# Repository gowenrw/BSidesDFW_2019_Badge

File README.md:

# BSidesDFW_2019_Akira_Badge

This is where all the files for the BSidesDFW 2019 Akira Badge will be stored.  
This includes code and art and cad and fab files.  All the things.

## File Structure

This is the file structure of this repository

* [/](/README.md) - YOU ARE HERE
* [/eda/](./eda/) - Electronic Design Automation files for the badge PCB (EDA is KiCad)
  * ./BSidesDFW_2019/ - KiCad 5.x project folder for the BSidesDFW 2019 badge
  * ./HHV_2019_SC/ - KiCad 5.x project folder for the HHV Soldering Challenge board
  * ./CH552G_dev_board/ - KiCad 5.x project folder for the CH552G development board
* [/code/](./code/) - Code for programming the badge
  * ./BSidesDFW_badge/ - Code for the BSidesDFW_2019_Badge
  * ./CH552G_dev_board/ - Code for the CH552G dev board
  * ./CH552T_dev_board/ - Code for the CH552T dev board designed by WrickertH552    
  * ./ugly_dev_board/ - Code for the Ugly Dev Board CH552 Proof of Concept
  * ./include/ - Includes for the 55X chipset used in all the above
* [/docs/](./docs/) - Documentation created by this project related to the badge
* [/graphics/](./graphics/) - Artwork and other graphics created by this project for the badge
* [/reference/](./reference/) - Documentation pulled from other sources related to the badge components
  * ./battery-holder/ - Reference Materials related to battery holders.
  * ./button/ - Reference Materials related to buttons.
  * ./capacitor/ - Reference Materials related to capacitors.
  * ./ch55x/ - Reference Materials related to the CH55x micro-controller.
  * ./LED/ - Reference Materials related to LEDs.
  * ./resistor/ - Reference Materials related to resistors.
  * ./switch/ - Reference Materials related to the switches.
  * ./USB-connector/ - Reference Materials related to USB connectors.
* ./README.md - This File
* ./LICENSE - Currently set to MIT but open to changing it

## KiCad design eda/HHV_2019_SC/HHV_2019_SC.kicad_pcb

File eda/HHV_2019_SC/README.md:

# BSidesDFW_2019_Badge / Electronic Design Automation / Hardware Hacking Village 2019 Soldering Challenge

This is where all the KiCad 5.x files related to the BSidesDFW Hardware Hacking Village 2019 Soldering Challenge board

## File Structure

This is the file structure of this repository

* [/](/README.md) - Home
* [/eda](/eda/) - Electronic Design Automation files for the badge PCB (EDA is KiCad)
  * [/eda/HHV_2019_SC/](/eda/HHV_2019_SC/) - YOU ARE HERE
    * ./<filename>.pro - project file. Holds parameters that apply to the entire project (schematic and PCB layout).
    * ./<filename>.sch - schematic file.
    * ./<filename>.kicad_pcb - the new PCB layout file.
    * ./<filename>.net - netlist in "Pcbnew" format
    * ./<filename>.bak - backup of schematic file.
    * ./<filename>.kicad_pcb-bak - backup of the new PCB layout file.
    * ./<filename>-cache.lib - a local cache copy of all the symbols used in the schematic
    * ./fp-lib-table - Footprint library list
    * ./sym-lib-table - Schematic library list
    * [./3d_models/](/eda/HHV_2019_SC/3d_models/) - This directory contains footprint 3d model files
    * [./gerber/](/eda/HHV_2019_SC/gerber/) - This directory contains gerber formatted files for manufacturing
    * [./lib_fp/](/eda/HHV_2019_SC/lib_fp/) - This directory contains footprint module directories
    * [./lib_sh/](/eda/HHV_2019_SC/lib_sh/) - This directory contains schematic library files
    * [./pdf/](/eda/HHV_2019_SC/pdf/) - This directory contains pdf prints of schematics and cad files

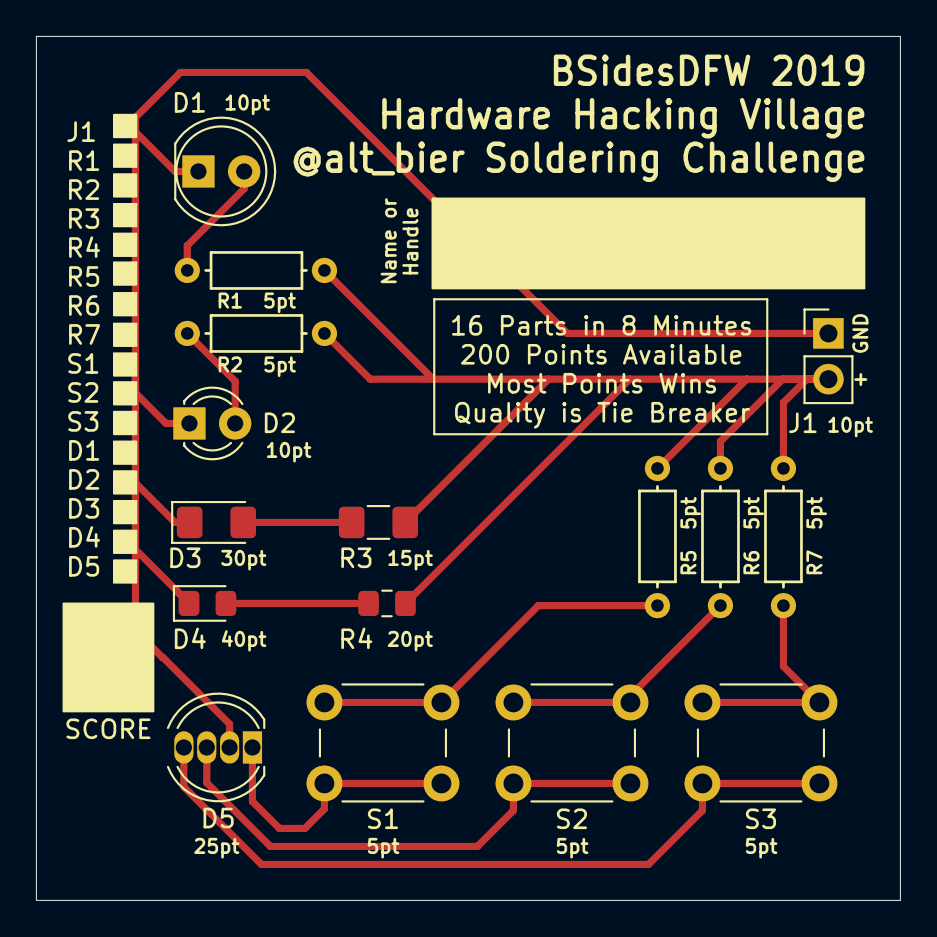
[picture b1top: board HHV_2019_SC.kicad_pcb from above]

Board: 2 copper layers, 48.0 x 48.0 mm, 16 parts (0 on the bottom side), 12 nets.

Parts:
D1: LED_5mm; LED_D5.0mm
D2: LED_3mm; LED_D3.0mm
D3: LED_1206; LED_1206_3216Metric_Pad1.42x1.75mm_HandSolder
D4: LED_0805; LED_0805_2012Metric_Pad1.15x1.40mm_HandSolder
D5: LED_RCBG_THT_5mm; LED_D5.0mm-4_RGB
J1: Battery_Connector; Pin_Header_Straight_1x02_Pitch2.54mm
R1, R2, R5, R6, R7: R_THT; R_Axial_DIN0207_L6.3mm_D2.5mm_P7.62mm_Horizontal
R3: R_1206; R_1206_3216Metric_Pad1.42x1.75mm_HandSolder
R4: R_0805; R_0805_2012Metric_Pad1.15x1.40mm_HandSolder
S1, S2, S3: SW_Push_Dual_THT_6mm; SW_PUSH_6mm

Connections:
GND: D1.1, D2.1, D3.1, D4.1, D5.2, J1.1
unnamed: D1.2, R1.2
unnamed: D2.2, R2.2
unnamed: D3.2, R3.2
unnamed: D4.2, R4.2
unnamed: D5.1, S1.1
unnamed: D5.3, S2.1
unnamed: D5.4, S3.1
unnamed: R5.2, S1.2
unnamed: R6.2, S2.2
unnamed: R7.2, S3.2
POS: J1.2, R1.1, R2.1, R3.1, R4.1, R5.1, R6.1, R7.1

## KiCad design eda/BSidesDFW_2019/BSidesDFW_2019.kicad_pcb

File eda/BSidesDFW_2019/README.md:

# BSidesDFW_2019_Badge / Electronic Design Automation / Main Badge

This is where all the KiCad 5.x files related to the main badge

## File Structure

This is the file structure of this repository

* [/](/README.md) - Home
* [/eda](/eda/) - Electronic Design Automation files for the badge PCB (EDA is KiCad)
  * [/eda/BSidesDFW_2019/](/eda/BSidesDFW_2019/) - YOU ARE HERE
    * ./<filename>.pro - project file. Holds parameters that apply to the entire project (schematic and PCB layout).
    * ./<filename>.sch - schematic file.
    * ./<filename>.kicad_pcb - the new PCB layout file.
    * ./<filename>.net - netlist in "Pcbnew" format
    * ./<filename>.bak - backup of schematic file.
    * ./<filename>.kicad_pcb-bak - backup of the new PCB layout file.
    * ./<filename>-cache.lib - a local cache copy of all the symbols used in the schematic
    * ./fp-lib-table - Footprint library list
    * ./sym-lib-table - Schematic library list
    * [./3d_models/](/eda/BSidesDFW_2019/3d_models/) - This directory contains footprint 3d model files
    * [./gerber/](/eda/BSidesDFW_2019/gerber/) - This directory contains gerber formatted files for manufacturing
    * [./lib_fp/](/eda/BSidesDFW_2019/lib_fp/) - This directory contains footprint module directories
    * [./lib_sh/](/eda/BSidesDFW_2019/lib_sh/) - This directory contains schematic library files
    * [./pdf/](/eda/BSidesDFW_2019/pdf/) - This directory contains pdf prints of schematics and cad files

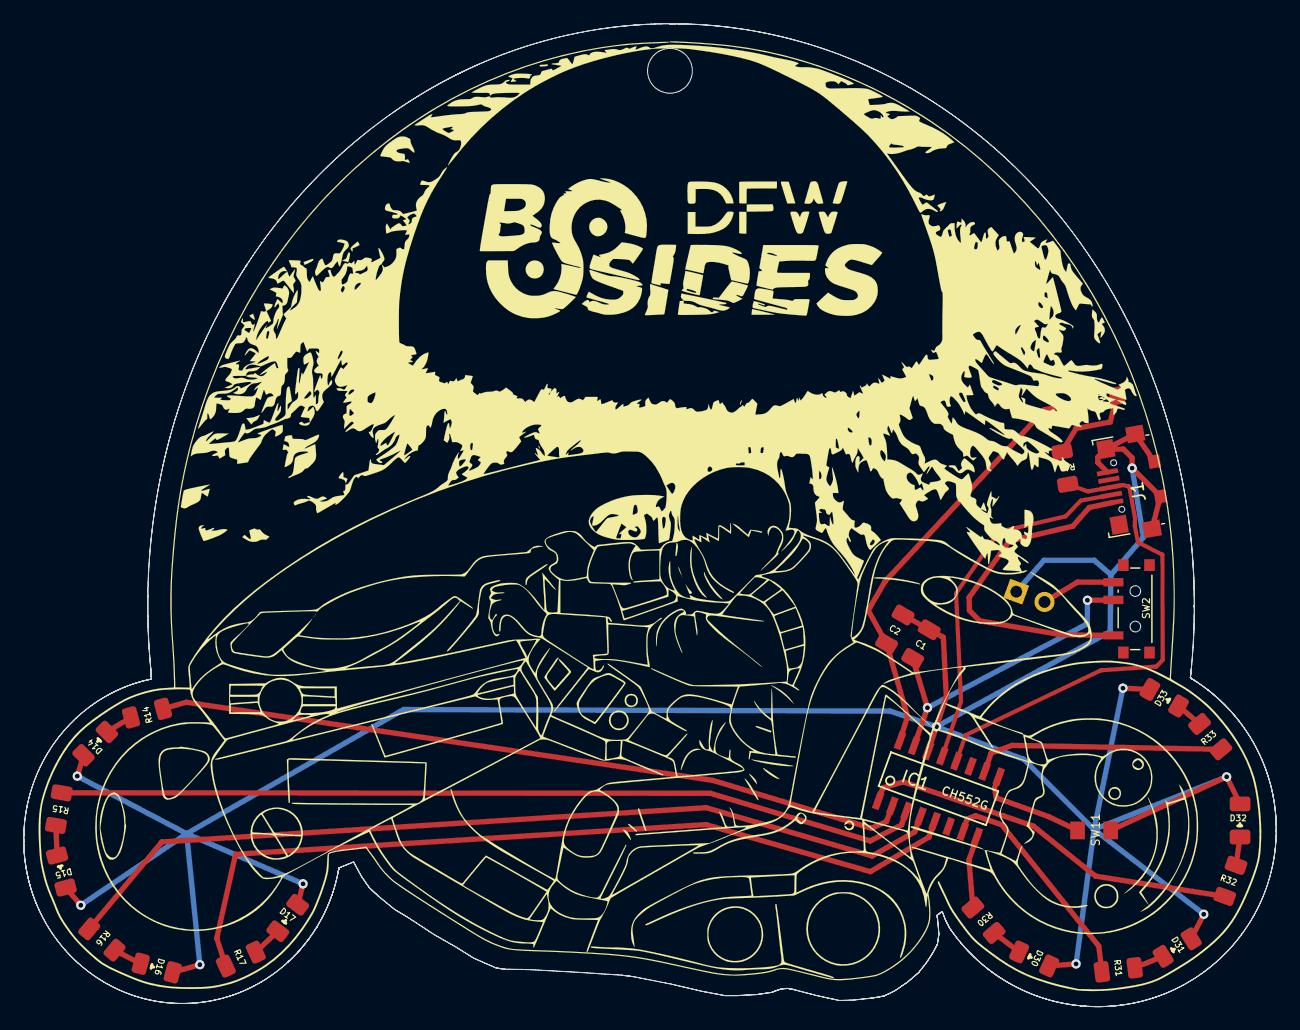
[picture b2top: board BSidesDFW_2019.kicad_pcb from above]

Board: 2 copper layers, 105.9 x 83.1 mm, 25 parts (0 on the bottom side), 25 nets.

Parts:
C1, C2: 0.1uF/100nF; C_1206_3216Metric
D14, D15, D16, D17: Red; LED_1206_3216Metric
D30, D31, D32, D33: Blue; LED_1206_3216Metric
IC1: CH552G; SOIC-16_3.9x9.9mm_Pitch1.27mm
J1: USB_B_Micro; USB_Micro-B_Jing
J2: Battery; Pin_Header_Straight_1x02_Pitch2.54mm
R1: 10k ohms; R_1206_3216Metric
R14, R15, R16, R17, R30, R31, R32, R33: 330 ohms; R_1206_3216Metric
SW1, SW11: TS2306A; TS2306A240GFMSM9_C388290
SW2: SW_SPDT_C136659; SW_SPDT_PCM12_C136659

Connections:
3V3: C2.2, IC1.16, SW1.1
BAT-PWR: J2.2, SW2.3
D+: IC1.12, J1.3, R1.1
D-: IC1.13, J1.2
GND: C1.1, C2.1, D14.1, D15.1, D16.1, D17.1, D30.1, D31.1, D32.1, D33.1, IC1.14, J1.5, J1.6, J2.1, SW11.2
unnamed: D14.2, R14.1
unnamed: D15.2, R15.1
unnamed: D16.2, R16.1
unnamed: D17.2, R17.1
unnamed: D30.2, R30.1
unnamed: D31.2, R31.1
unnamed: D32.2, R32.1
unnamed: D33.2, R33.1
unnamed: R1.2, SW1.2
P1.1: IC1.9, SW11.1
P1.4: IC1.2, R14.2
P1.5: IC1.3, R15.2
P1.6: IC1.4, R16.2
P1.7: IC1.5, R17.2
P3.0: IC1.8, R30.2
P3.1: IC1.7, R31.2
P3.2: IC1.1, R32.2
P3.3: IC1.10, R33.2
USB-PWR: J1.1, SW2.1
VCC: C1.2, IC1.15, SW2.2

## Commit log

2019-08-16 Add LICENSE
2019-08-16 readme-update
2019-08-16 ideas
2019-08-19 file_structure_added
2019-08-19 A start at some file structure documentation
2019-08-19 Markdown path issues gitlab vs github
2019-08-19 Updated main readme
2019-08-19 documentation
2019-08-19 Code documentation
2019-08-19 Graphics doc update
2019-08-19 docs
2019-08-20 CH55x reference information
2019-08-20 Akira Bike Images for possible badge shape
2019-08-20 Started KiCad layout for prototype PCB
2019-08-21 added_chat_link
2019-08-21 Added component reference docs
2019-08-23 component-footprints
2019-08-25 more-component-details
2019-08-26 Added gitignore file
2019-08-26 Started documenting coding procedures for CH55x
2019-08-27 Initial code push
2019-08-27 AAA Battery Holder Reference
2019-09-04 Code fopr the CH552T dev board
2019-09-05 Development board work
2019-09-06 More dev board work
2019-09-06 Dev board schematic complete and pcb started
2019-09-07 CH552G dev board complete
2019-09-09 Logo Updates
2019-09-09 Started on the HHV Soldering Challenge PCB
2019-09-09 More work on HHV SC PCB
2019-09-09 HHV SC PCB updates
2019-09-14 CH552G Dev board update
2019-09-17 Started Badge Art
2019-09-18 More badge art work.
2019-09-18 New code for the CH552G dev board
2019-09-19 Using CH552G_dev as template for BSidesDFW_2019 KiCad PCB design.
2019-09-20 Completed edge cuts for badge PCB
2019-09-27 First pass of badge pcb complete
2019-09-27 Final design pass of badge PCB
2019-09-29 Badge PCB Prototypes Ready
2019-10-02 New firmware code for the BSidesDFW badge
2019-10-04 Repositoriy cleanup
2019-10-05 Readme correction
2019-10-05 docs update
2019-10-05 Set theme jekyll-theme-hacker
2019-10-07 Soldering Challenge PCB Complete.
2019-10-13 Lanyard graphics
2019-10-22 code prep for crypto challenge
2019-10-22 web page prep
2019-10-23 eda documnet updates
2019-10-23 Create CNAME
2019-10-24 Web page updates
2019-10-24 More Web Page Updates
2019-11-13 Crypto Challenge Details
2019-11-14 Badge code hacks by @leetnet
2020-04-29 Dev board code for testing
2022-11-07 Added binaries
2023-01-28 old staged files
